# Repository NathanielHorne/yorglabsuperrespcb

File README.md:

# yorglabsuperrespcb

# Table of Contents
1. [SUMMARY](#SUMMARY)
2. [PCB](#PCB)
3. [CODE](#CODE)
4. [OPERATION](#OPERATION)

## SUMMARY

## PCB
  ### Overview

  The PCB looks nasty, but is more simple than it appears, at first.
  ***
  ### Where Was it Milled?
  Just as some general background, the board was milled and cut out at the BYU Electrical Engineering Experiential Learning Center. At the time of manufacture, they had yet to integrate solder masks. So, any pictures given of the fully-assembled board will show only *bare copper*. Future iterations should have a solder mask for safety reasons.
  ***
  ### Tension Relief Holes

  Probably the most striking thing to see, at first, are the tension relief holes. You thread the wires or ribbon cables through them like a needle and thread. This makes it so that the tension of any motion / movement on the wires from the outside is transfered to the board instead of the connectors. This adds durability to the board, but also makes it so that it's more complicated to manufacture. Luckily, the BYU Electrical Engineering Experiential Learning Center was able to mill it with little issue.
  ***
  ### Mounting Holes

  These help mount the PCB to a backing plate. These aren't utilized in our current setup.
  ***
  ### Power Network
  
  ***
  ### Signal Network

  A note about the joystick: the joystick is comprised of two potentiometers (variable resistors). The Nano is able to convert voltage inputs from 0V - 5V and convert it to a value of 0 - 1024 using `analogRead([pin name])`. By running the output of the variable end of the potentiometer to a pin corresponding to the X and Y axis, we're able to measure the angle at which the joystick is currently at. This helps to inform the speed each motor takes on. The more extreme the angle of the joystick on a particular axis, the faster the motor on that particular axis is.
  ***

## CODE
  ### Limitations
  The code isn't perfect. Memory leaks and other performance issues may exist. In addition, the code doesn't neccessarily *need* to be in a single file. Other issues may exist to others. Input in the "issues" page of this repo would be much appreciated. Because an arduino nano cannot support multithreading, minimizing memory leaks and improving speeds are paramount.

  The photogates also aren't used, currently. Therefore, there is no safety preventing the device from moving beyond its intended limits. This is a *major* bug that needs to be fixed immediately.
  ***
  ### Methodology
  In general, any variable used is either inumerated using the `#define` command or is passed by reference. This helps improve the speed at which the code iterates and the amount of memory used. These things can still be improved upon, however.
  ***
  This code is broken up into three distinct sections: perception, planning, and action.
  ```cpp
  perception();
  ```
  This is where the inputs from the various sensors the nano uses are measured and saved. Currently, just the input of the joystick is read, but in the future, this is where one would check whether or not the laser gates are tripped or not, for example.
  ```cpp
  planning();
  ```
  This is where actions are prepped. In our case, this is where the direction and speed of the stepper motors is calculated.
  ```cpp
  action();
  ```
  In this section, the nano executes the actions we had prepared.
  
  *Every other method in the code is an appendage to these three methods*
  
  ***
  ### Startup
  An attempt was made to create a movement sequence that would automatically "home" the stage, setting the stepper's default state to one extreme of their movement. This would allow the laser gates to prevent the stage from moving beyond their limits. This was never acheived. This also makes it so that the I2C display doesn't display location information (another desired goal with startup)
  ### Custom Step Signal
  In order for each stepper to increment, the "step" pin needs to receive a distinct off-on-off pattern. The rate at which these patterns come in dictates the rate at which the stepper increments, changing its speed. 
  The Arduino Nano's hardware natively supports "pulse width modulation" (PWM) that *could* be used to accomplish this. However, PWM signals are generally set at a specific frequency. This would make it so that the steppers would step at a fixed rate regardless of the joystick's orientation. 
  
  Because of these limitations, a way of delivering this signal was created using the Nano's internal clock and digital pins:
  ```cpp
  void move_stepper(const unsigned int& step_pin, unsigned long& time_index, const unsigned int& time_tolerance, const unsigned int& direction_bool, int64_t& num_steps, const int& ena) {
    if ((micros() - time_index) > time_tolerance) {
      digitalWrite(step_pin, HIGH);
      digitalWrite(step_pin, LOW);
      if (ena == LOW) {
        if(direction_bool == HIGH) {
          num_steps++;
        }
        else if (direction_bool == LOW) {
          num_steps--;
        }
      }
      time_index = micros();
    }
  }
  ```
  At its core, this method manually defines how long the arduino takes in-between stepping each motor. This is done by storing when the nano begins to wait using the `micros();` command, then measuring how much time has past. If the elapsed time is larger than the defined wait time, the nano commands the stepper to take a single step, the number of total steps that stepper has taken is recorded, and the process begins again. 
  The wait time is defined at the very top of the file. See the variables `slowest_speed`, `second_fastest`, `second_slowest`, and `fastest_speed` in the `#define` section of the code.
  ***
  ### A Note About Printing the Relative Position of the Stage
  In the event that we wanted to plot the relative position of the stage, we would need to display the number of steps the stepper has taken in relation to when it was homed. Turns out, the number of steps a stepper takes traversing accross one of the metal fins the photodiode uses to tell whether or not the stepper is out of alignment is about the max value of the variable type "long long" or "int64_t". Obviously, this is kind of insane. It also leads to other errors. 
  ***
## OPERATION
Ensure every wire is connected to where it needs to be connected to. Position the stage so the path of the photodiodes is blocked by their corresponding metal fin. Plug the stage's power supply into a wall socket. Turn the motherboard on by flipping the switch. A blue and red indicator light from the buck converter and Arduino Nano respectively should come on immediately. From then on, use the joystick to move the stage. The higher the angle of the joystick in either direction, the faster the steppers will step in that direction.

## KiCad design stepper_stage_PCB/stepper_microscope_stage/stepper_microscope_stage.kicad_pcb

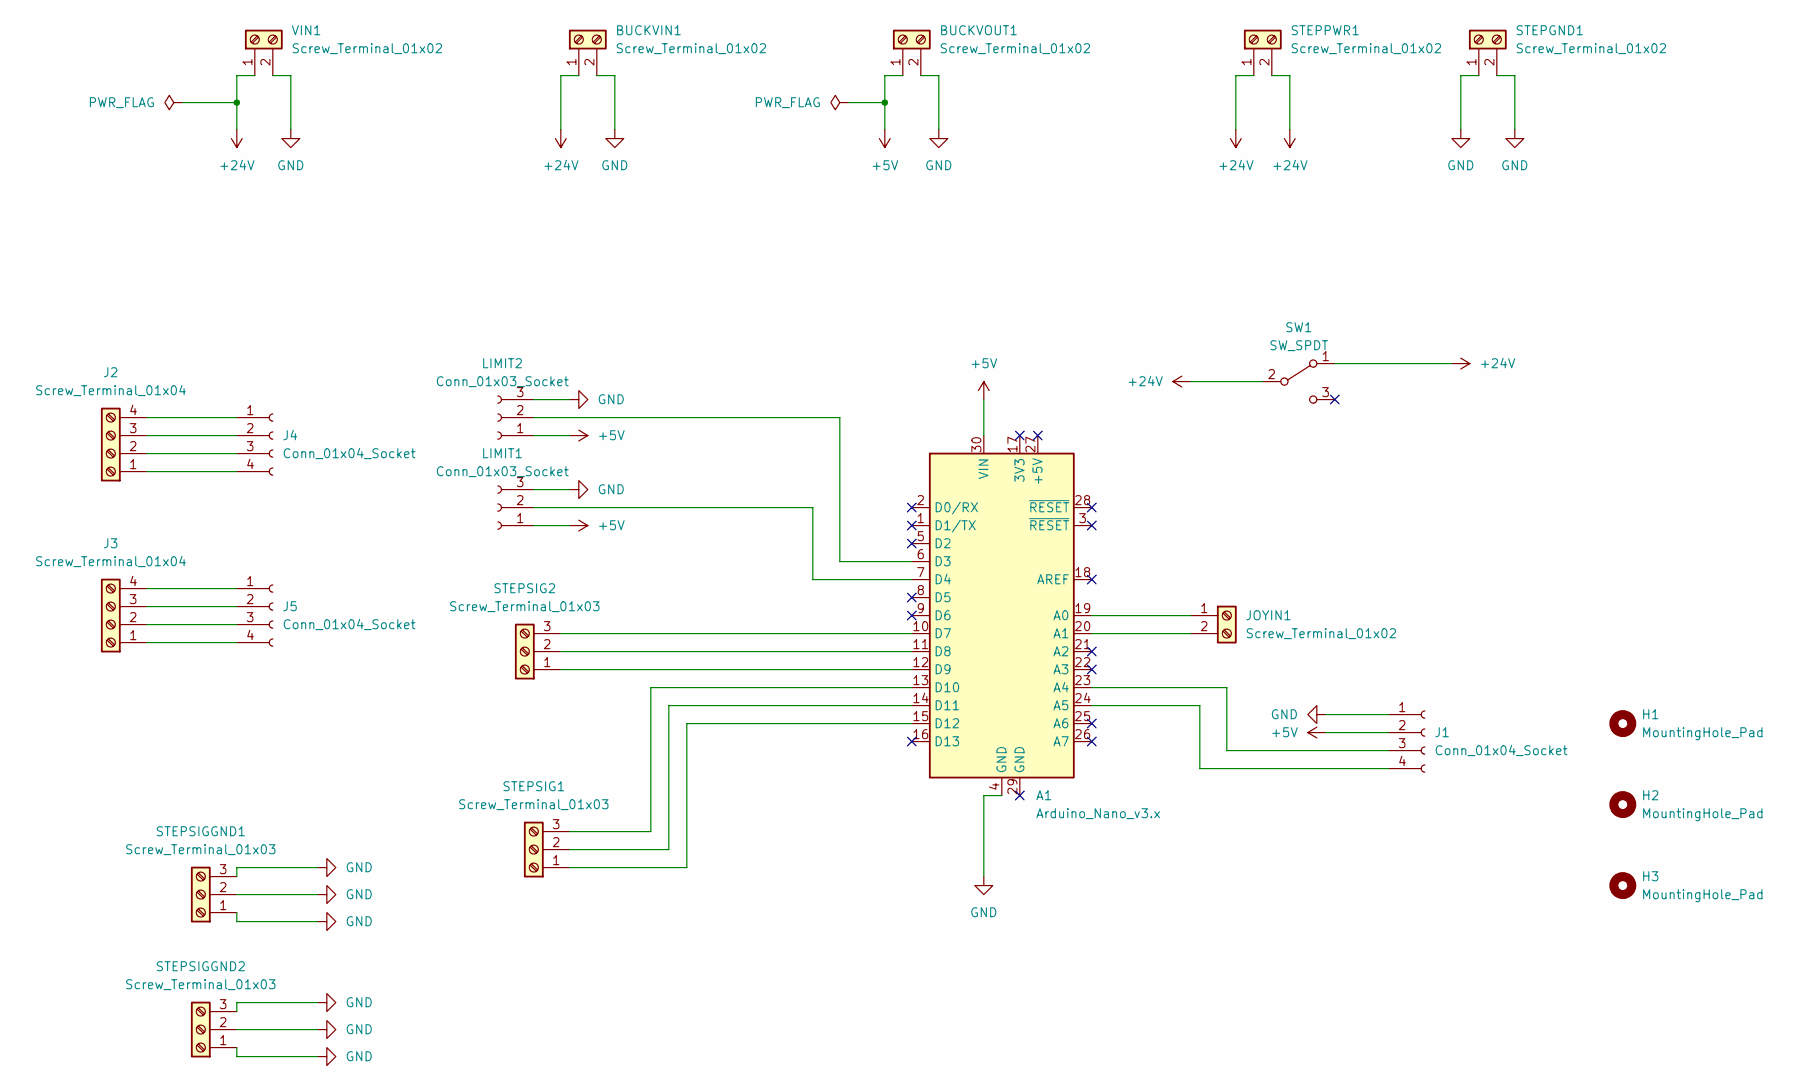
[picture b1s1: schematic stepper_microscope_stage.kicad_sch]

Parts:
A1: Arduino_Nano_v3.x; Arduino_Nano
BUCKVIN1: Screw_Terminal_01x02; TerminalBlock_Altech_AK300-2_P5.00mm
BUCKVOUT1: Screw_Terminal_01x02; TerminalBlock_Altech_AK300-2_P5.00mm
H1, H2, H3: MountingHole_Pad; MountingHole_4.3mm_M4_Pad
J1: Conn_01x04_Socket; PinSocket_1x04_P2.54mm_Vertical
J2, J3: Screw_Terminal_01x04; TerminalBlock_Altech_AK300-4_P5.00mm
J4, J5: Conn_01x04_Socket; JST_EH_B4B-EH-A_1x04_P2.50mm_Vertical
JOYIN1: Screw_Terminal_01x02; TerminalBlock_Altech_AK300-2_P5.00mm
LIMIT1, LIMIT2: Conn_01x03_Socket; JST_EH_B3B-EH-A_1x03_P2.50mm_Vertical
STEPGND1: Screw_Terminal_01x02; TerminalBlock_Altech_AK300-2_P5.00mm
STEPPWR1: Screw_Terminal_01x02; TerminalBlock_Altech_AK300-2_P5.00mm
STEPSIG1, STEPSIG2: Screw_Terminal_01x03; TerminalBlock_Altech_AK300-3_P5.00mm
STEPSIGGND1, STEPSIGGND2: Screw_Terminal_01x03; TerminalBlock_Altech_AK300-3_P5.00mm
SW1: SW_SPDT; spdt_4mm_pitch_with_tension_relief
VIN1: Screw_Terminal_01x02; TerminalBlock_Altech_AK300-2_P5.00mm

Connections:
+5V: A1.30 (VIN), BUCKVOUT1.1, J1.2, LIMIT1.1, LIMIT2.1
+24V: BUCKVIN1.1, STEPPWR1.1, STEPPWR1.2, SW1.1 (A), SW1.2 (B), VIN1.1
GND: A1.4 (GND), BUCKVIN1.2, BUCKVOUT1.2, J1.1, LIMIT1.3, LIMIT2.3, STEPGND1.1, STEPGND1.2, STEPSIGGND1.1, STEPSIGGND1.2, STEPSIGGND1.3, STEPSIGGND2.1, STEPSIGGND2.2, STEPSIGGND2.3, VIN1.2
unnamed: A1.19 (A0), JOYIN1.1
unnamed: A1.20 (A1), JOYIN1.2
unnamed: A1.23 (A4), J1.3
unnamed: A1.24 (A5), J1.4
unnamed: A1.6 (D3), LIMIT2.2
unnamed: A1.7 (D4), LIMIT1.2
unnamed: A1.10 (D7), STEPSIG2.3
unnamed: A1.11 (D8), STEPSIG2.2
unnamed: A1.12 (D9), STEPSIG2.1
unnamed: A1.13 (D10), STEPSIG1.3
unnamed: A1.14 (D11), STEPSIG1.2
unnamed: A1.15 (D12), STEPSIG1.1
unnamed: J2.1, J4.4
unnamed: J2.2, J4.3
unnamed: J2.3, J4.2
unnamed: J2.4, J4.1
unnamed: J3.1, J5.4
unnamed: J3.2, J5.3
unnamed: J3.3, J5.2
unnamed: J3.4, J5.1

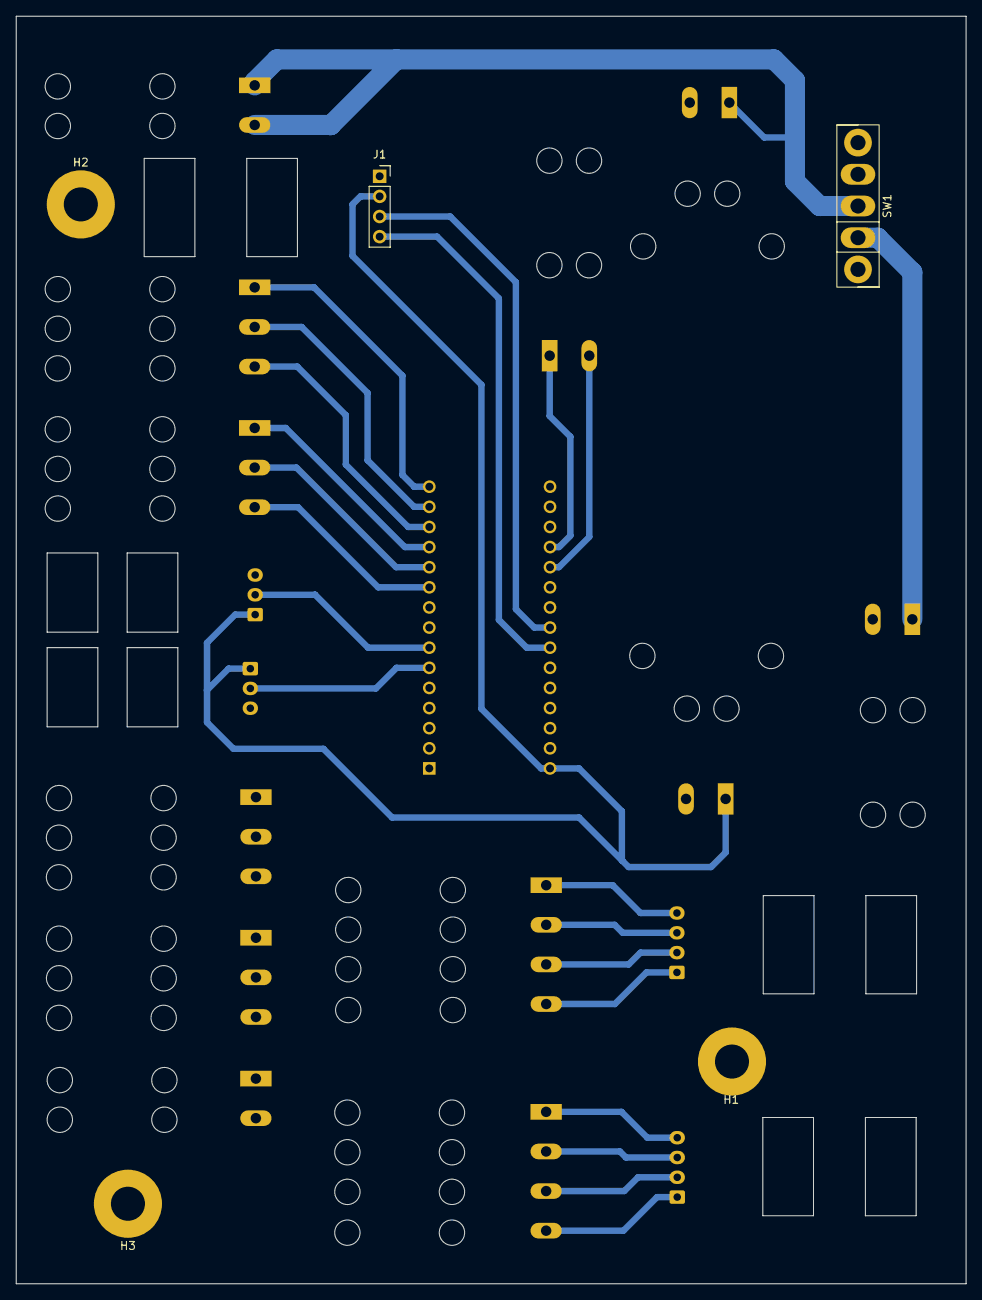
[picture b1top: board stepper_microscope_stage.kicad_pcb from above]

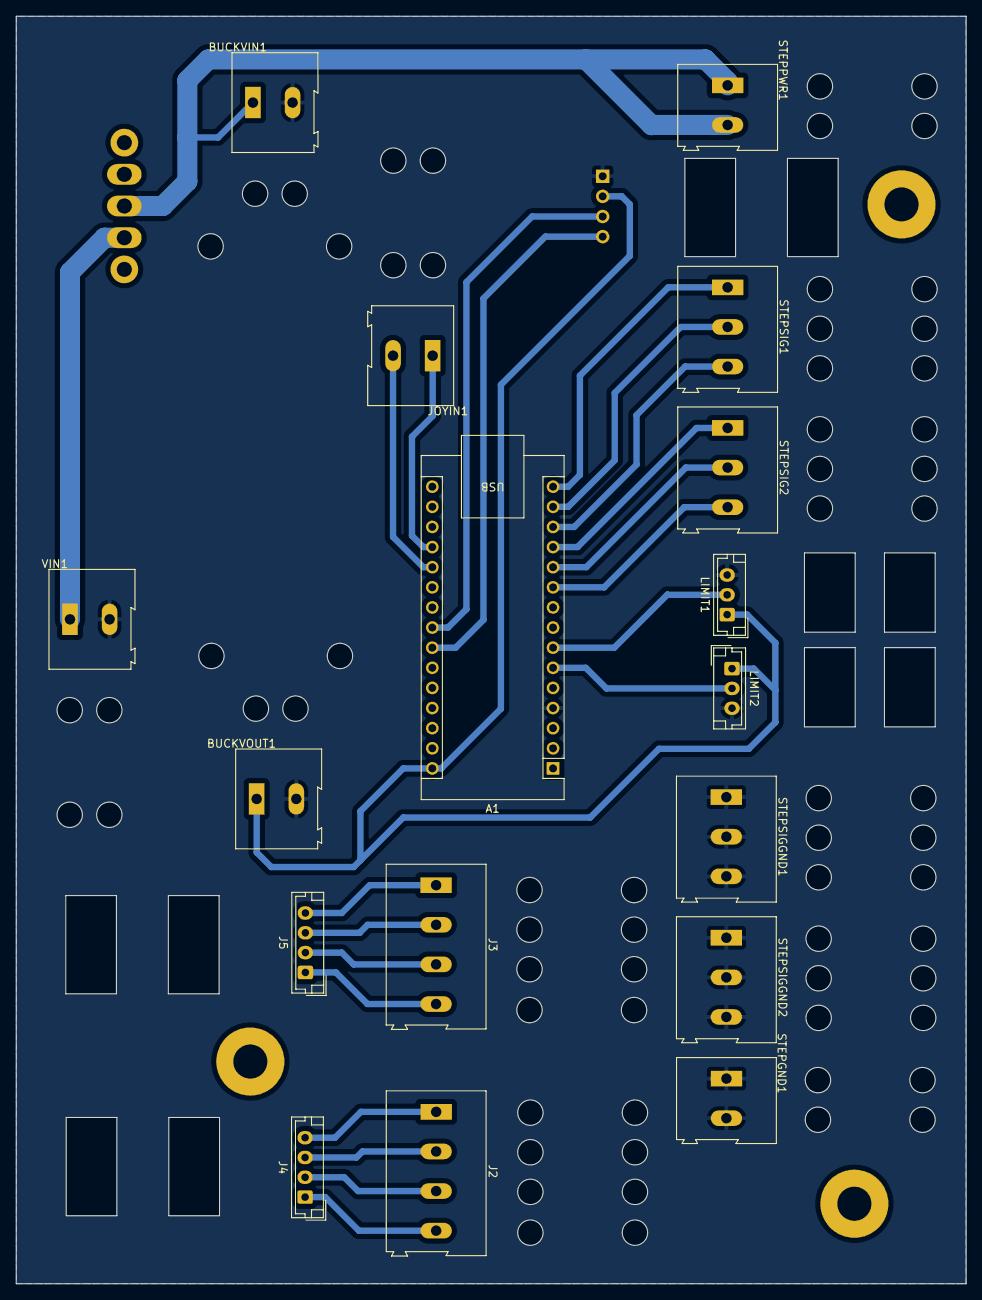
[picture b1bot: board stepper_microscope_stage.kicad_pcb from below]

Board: 2 copper layers, 119.9 x 160.0 mm, 22 parts (17 on the bottom side), 23 nets.

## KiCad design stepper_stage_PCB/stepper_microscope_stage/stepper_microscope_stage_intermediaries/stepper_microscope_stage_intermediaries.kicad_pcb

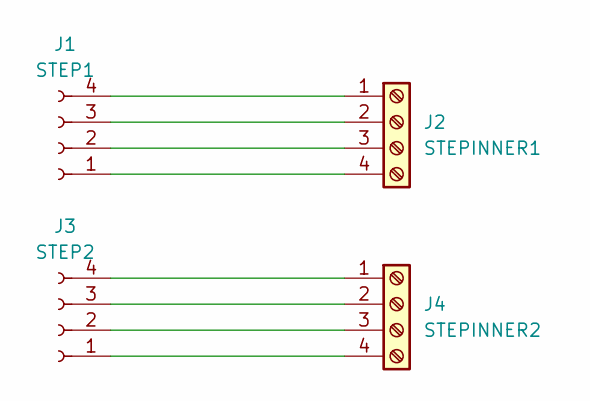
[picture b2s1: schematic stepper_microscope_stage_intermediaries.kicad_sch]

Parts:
J1: STEP1; Molex_CLIK-Mate_502382-0470_1x04-1MP_P1.25mm_Vertical
J2: STEPINNER1; TerminalBlock_Altech_AK300-4_P5.00mm
J3: STEP2; Molex_CLIK-Mate_502382-0470_1x04-1MP_P1.25mm_Vertical
J4: STEPINNER2; TerminalBlock_Altech_AK300-4_P5.00mm

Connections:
unnamed: J1.1, J2.4
unnamed: J1.2, J2.3
unnamed: J1.3, J2.2
unnamed: J1.4, J2.1
unnamed: J3.1, J4.4
unnamed: J3.2, J4.3
unnamed: J3.3, J4.2
unnamed: J3.4, J4.1

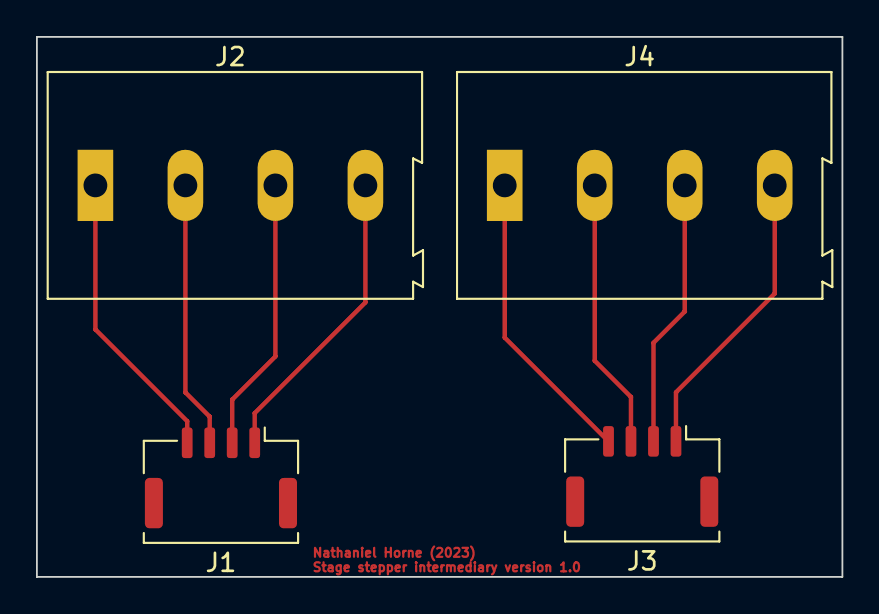
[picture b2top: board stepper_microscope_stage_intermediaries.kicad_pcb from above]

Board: 2 copper layers, 44.8 x 30.0 mm, 4 parts (0 on the bottom side), 8 nets.

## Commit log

2023-09-08 Moved existing work to GitHub.
2023-09-08 Updated mounting holes to be M4 instead of M2
2023-09-08 Route GND of +24v net.
2023-09-08 Tried to make some more changes, but git revert threw a fit so here we are
2023-09-08 Final 90%
2023-09-08 Routed and filled board. Missing switch
2023-09-09 Version 1 acheived!
2023-09-27 Working. Must add following: (1) LCD space (2) ground plane
2023-09-28 Large, but works
2023-09-29 Experimented with smaller PCB. Reorganized directories to be more clean
2023-09-29 Forgot to save work. Autosaved backup.
2023-11-22 Version 0
    Updated PCB, milled that PCB, soldered parts to that PCB, updated code, works as expected except for the following functionalities listed below:
    - Laser gates are non-operational as of yet. This leads to the following:
    - No homing functionality yet
    - No safety measures to ensure the steppers avoid grinding on their bearings
    - True logarithmic speed control
    - Suitable housing
2023-11-25 Homing behavior achieved.
2024-04-26 Update README.md
    Trying to do fancy editing. Will see how long this will take. Will adjust timing accordingly
2024-04-26 Started editing the README
2024-04-26 Added tension relief indications and where the board was milled.
2024-05-02 Reached stopping point with README. Started commenting code.
2024-05-02 Added future subheadings for code descriptions.
2024-05-02 Added methodology subsection.
2024-05-02 Added headers for PWM sig and startup features. Started editing PWM sig.
2024-05-13 Finished first draft.
2024-05-13 Fixed TOC links.
2024-05-13 Wrote comments in code.
